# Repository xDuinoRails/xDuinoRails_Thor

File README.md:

# mtc21/plux16 Semi-Decoder for Seeed XIAO boards

Make a Seeed XIAO board a mtc21 decoder, all the electronics needed is on this little board:
- mtc21/plux16 compatible connector
- DC Motor
- 2x Functions
- DCC / DCC-ACK / RailCom

Open-Source [schematics](xDuinoRails-Thor-M-schematic.pdf) and [PCB design](xDuinoRails-Thor-M-PCB_All.pdf) included.

## Wiring

```
                     +--------------------+      +--------------------+         +---------------+
                     |      RP2040        |      |     BDR-6133       |         |     Motor     |
                     |    (Top View)      |      |    Motor Driver    |         | DC brushed    |
                     +--------------------+      +--------------------+         +---------------+
                     |                5v  |      |                    |         |               |
          ---``|<----| D15 (LED)      GND |      |                    |         |               |
          ---``|<----| D16 (LED)      3v3 |      |                    |         |               |
                     |                    |      |                    |         |               |
                     |        (PWM B) D8  |----->| InB           OutB |=====+==>| B             |
                     |        (PWM A) D7  |----->| InA           OutA |==+==|==>| A             |
                     |                    |      +---------+----------+  |  |   +---------------+
                     |       (Shut)   A2  |<.............../             |  |
                     |       (bEMF B) A1  |<----------------------------/   |
                     |       (bEMF A) A0  |<-------------------------------/
                     |                    |
                     |                    |      +--------------------+
                     |                    |      | Functions          |
                     |                    |      +--------------------+
                     |         F0f    D9  |----->| F0f                |
                     |         F0b    D10 |----->| F0b                |
                     |                    |      +---------+----------+
                     |       (Shut)   A3  |<.............../

                     |                    |      +--------------------+
                     |                    |      | DCC / Railcom      |
                     |                    |      +--------------------+
                     |     DCC-ACK    D4  |----->| DCC-ACK            |
                     |     DCC/MM/SX  D5  |<-----| DCC/MM/SX          |
                     |     RailCom    D6  |----->| RailCom            |
                     |                    |      +---------+----------+
                     |       (Shut)   A3  |<.............../
                     +--------------------+
```

## Purchase your copy

If you want an easy way to try this board, order one on tindie:
- https://www.tindie.com/products/chatelao/diy-dccmm-decoder-for-xiao-boards

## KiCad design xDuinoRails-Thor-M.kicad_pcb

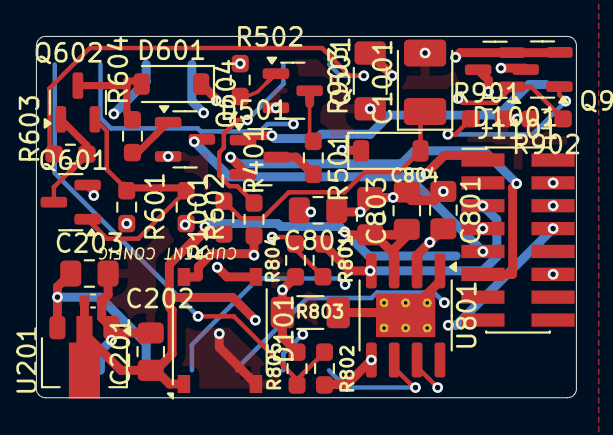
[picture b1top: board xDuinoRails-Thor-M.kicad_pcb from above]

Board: 6 copper layers, 30.0 x 20.1 mm, 38 parts (1 on the bottom side), 28 nets.

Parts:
C201: 22uF; C_0805_2012Metric_Pad1.18x1.45mm_HandSolder
C202: 1u; C_0402_1005Metric
C203: 47uF; C_0805_2012Metric_Pad1.18x1.45mm_HandSolder
C801, C804: 100nF; C_0805_2012Metric_Pad1.18x1.45mm_HandSolder
C802, C803: 10uF; C_0805_2012Metric_Pad1.18x1.45mm_HandSolder
C1001: 100uF; CP_EIA-3528-21_Kemet-B_Pad1.50x2.35mm_HandSolder
D101: ABS210; Diode_Bridge_Diotec_ABS
D501: BAT54C; 8x50_SOT-23
D601, D1001: 1N5819W; D_SOD-123
J1101: Conn_02x08_Odd_Even; PinHeader_2x08_P1.27mm_Vertical_SMD
Q501, Q604: S8050; 8x50_SOT-23
Q601, Q602: S8550; 8x50_SOT-23
Q901, Q902: BSS138; SOT-23
R401: 33k; R_0603_1608Metric_Pad0.98x0.95mm_HandSolder
R501, R1001: 100R; R_0603_1608Metric_Pad0.98x0.95mm_HandSolder
R502, R603, R604, R901, R902: 10k; R_0603_1608Metric_Pad0.98x0.95mm_HandSolder
R601: 20R; R_0603_1608Metric_Pad0.98x0.95mm_HandSolder
R602: 1M; R_0603_1608Metric_Pad0.98x0.95mm_HandSolder
R801, R802: 6k8; R_0603_1608Metric_Pad0.98x0.95mm_HandSolder
R803, R903: 0R1; R_1206_3216Metric_Pad1.30x1.75mm_HandSolder
R804, R805: 1k; R_0603_1608Metric_Pad0.98x0.95mm_HandSolder
U201: HT75xx-1-SOT89; SOT-89-3
U801: BDR6133; SOIC-8-1EP_3.9x4.9mm_P1.27mm_EP2.41x3.3mm_ThermalVias
U1301: MOUDLE-SEEEDUINO-XIAO; XIAO_SMD

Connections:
/+3V3: C203.1, C801.1, C802.2, Q601.1 (E), R601.2, R602.2, U201.3 (VOUT), U801.2 (VCC), U1301.12 (3V3)
/+U: C201.1, C202.1, C803.1, C804.1, D101.1 (+), D1001.1 (K), J1101.8, R1001.1, U201.2 (VIN), U801.3 (VM)
/AMP_FUNC0: J1101.6, Q901.3 (D)
/AMP_FUNC1: J1101.12, Q902.3 (D)
/AMP_MOTOR0: J1101.5, R801.2, U801.4 (OUTA)
/AMP_MOTOR1: J1101.7, R802.2, U801.5 (OUTB)
/DCC0: D101.3, D501.1, D601.1 (K), J1101.11
/DCC1: D101.4, D501.2, J1101.9, Q604.3 (C), R401.1
/DCC_ACK: R502.1, U1301.5 (PA8_A4_D4_SDA)
/DCC_MM_SIGNAL: R401.2, U1301.6 (PA9_A5_D5_SCL)
/EMF_MOTOR0: R801.1, R804.1, U1301.2 (PA4_A1_D1)
/EMF_MOTOR1: R802.1, R805.1, U1301.1 (PA02_A0_D0)
/FUNC0: Q901.1 (G), R901.1, U1301.11 (PA6_A10_D10_MOSI)
/FUNC1: Q902.1 (G), R902.1, U1301.10 (PA5_A9_D9_MISO)
/I_FUNC: Q901.2 (S), Q902.2 (S), R903.2, U1301.4 (PA11_A3_D3)
/MOTOR0: U801.6 (INA), U1301.8 (PB09_A7_D7_RX)
/MOTOR1: U801.7 (INB), U1301.9 (PA7_A8_D8_SCK)
/RAILCOM_DATA: R603.2, U1301.7 (PB08_A6_D6_TX)
/rails_signal_combined-medium/rails-signal-acknowledge_dcc/DCC+: D501.3, R501.2
/rails_signal_combined-medium/rails-signal-acknowledge_dcc/DCC+_DROP: Q501.3 (C), R501.1
/rails_signal_combined-medium/rails-signal-acknowledge_dcc/DCC_ACK_IN: Q501.2 (B), R502.2
/rails_signal_combined-medium/rails_signal_feedback_dcc-railcom-8x50/RC_CURR: Q601.2 (B), Q602.1 (E), R601.1, R602.1
/rails_signal_combined-medium/rails_signal_feedback_dcc-railcom-8x50/RC_DATA_IN: Q601.3 (C), Q602.2 (B), R603.1
/rails_signal_combined-medium/rails_signal_feedback_dcc-railcom-8x50/RC_SIGNAL: D601.2 (A), Q602.3 (C), R604.1
GND: C201.2, C202.2, C203.2, C801.2, C802.1, C803.2, C804.2, C1001.2, D101.2 (-), J1101.4, Q501.1 (E), Q604.1 (E), R803.1, R804.2, R805.2, R901.2, R902.2, R903.1, U201.1 (GND), U1301.13 (GND)
unnamed: C1001.1, D1001.2 (A), R1001.2
unnamed: Q604.2 (B), R604.2
PGND: R803.2, U801.1 (GND), U801.9 (PGND), U1301.3 (PA10_A2_D2)

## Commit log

2026-01-12 Add kibot.yaml configuration for PCB generation
2026-01-12 Add KiCad DRC and ERC checks workflow
    This workflow performs DRC and ERC checks for KiCad projects, uploads artifacts, and creates a release if a version tag is pushed.
2026-01-12 Add - initial version
2026-01-12 Fix - Remove ERC error, refresh annotation
2026-01-12 Fix - revert to working model
2026-01-12 Fix - Yellow background on subcircuits
2026-01-12 Add - Fix ERC errors
2026-01-12 Fix - Remove backups
2026-01-12 Fix - Extend .gitignore
2026-01-12 Fix - Ignore problems in subsheet
2026-01-12 Change PDF format to lowercase pdf in kibot.yaml
2026-01-12 Change output format from PDF to SVG in kibot.yaml
2026-01-12 Modify fields in kibot.yaml
    Removed LCSC and Quantity fields, added OLI_ID field.
2026-01-12 Change output format and file naming in kibot.yaml
2026-01-12 Remove 'dir' property from multiple entries in kibot.yaml
2026-01-12 Update kibot.yaml to add Gerber options
    Added options to suppress footprint references and values in Gerber files.
2026-01-12 Add interactive BOM generation configuration
2026-01-12 Fix - Position of labels
2026-01-12 Update show_fields and group_fields format
    Changed show_fields and group_fields to comma-separated strings.
2026-01-12 Fix - Move labels to the right place
2026-01-12 Fix - BOM errors
2026-01-12 Rename CONTROBUTING.md to CONTRIBUTING.md
2026-01-12 Add licensing information to LICENSE.md
    This document outlines the dual licensing structure of the project, including details on both open-source and commercial licensing options, along with the associated benefits.
2026-01-13 Enhance kibot.yaml with filters and 3D render options
    Added filters and new rendering options for 3D views.
2026-01-13 Enhance GitHub Actions workflow with Pinion config check
    Added a step to find Pinion config and conditionally run Pinion rendering. Updated artifact upload process.
2026-01-13 Clean up xDuinoRails-Thor-M.pinion.yaml
    Removed unnecessary blank lines from the YAML file.
2026-01-13 Remove 'Archive' task from kibot.yaml
    Removed the 'Archive' task that creates a ZIP file with documentation.
2026-01-13 Rename xDuinoRails-Thor-M-3D_Top.png to imagesimages/xDuinoRails-Thor-M-3D_Top.png
2026-01-13 Rename xDuinoRails-Thor-M-3D_Top.png to xDuinoRails-Thor-M-3D_Top.png
2026-01-13 Add README with project description and purchase link
2026-01-13 Refactor 3D view settings in kibot.yaml
    Removed '3D_Top_View_Clean' configuration and adjusted dimensions for '3D_Top_View' and '3D_Bottom_View'.
2026-01-13 Include wiring section in README
    Added wiring diagram for RP2040 and motor driver setup.
2026-01-13 Update README with schematics and PCB design links
    Added links to open-source schematics and PCB design.
2026-01-13 Correct capitalization of 'schematics' in README
2026-01-13 Fix - 100nF capacitor size
2026-01-16 Fix - 3D model and some silkscreen
2026-01-17 Chg - Draft of Plux16 connector
2026-01-17 Add - Routing of PluX16 connector
2026-01-17 Add - New annotations of schematics
2026-01-17 Fix - ERC errors
2026-01-17 Add - Plux16 partnumber
2026-01-18 Add - plux16 integration v0.9
2026-01-19 Change contact email in LICENSE.md
    Updated contact information for commercial inquiries.
2026-01-19 Update README with new 3D images
    Added additional images to README for better visualization.
2026-01-19 Add ref_separator option to kibot.yaml
2026-01-19 Remove duplicate OLI_ID field from kibot.yaml
2026-01-19 Rename 'Reference' to 'Ref' in kibot.yaml
2026-01-19 Add production_variant to kibot.yaml
2026-01-19 Reintroduce production_variant and update render views
    Reintroduced the 'production_variant' and updated its position. Added 'clean_render_variant' to '3D_Top_View' and '3D_Bottom_View'.
2026-01-19 Remove variant from 3D view configurations
2026-01-19 Add pre_transform option to render configurations
2026-01-20 Fix - Component size for 100nF
2026-01-21 Add rotation correction data for various components
2026-01-21 Add remote workflow trigger on main branch push
    Added a new job to trigger a remote workflow on push to the main branch.
2026-01-21 Update workflow to trigger xDuinoRails_Thor_Prod
2026-01-21 Remove unused PCB export configurations
    Removed several PCB printing and export configurations from the kibot.yaml file.
2026-01-21 Increase render dimensions in kibot.yaml
2026-01-21 Simplify kicad-checks.yml by removing pinion scripts
    Removed pre-launch and post-launch scripts for pinion installation and execution.
